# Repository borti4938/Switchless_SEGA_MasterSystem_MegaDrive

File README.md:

### Switchless Mods for SEGA MasterSystem and MegaDrive
---

This is a collection of earlier projects. These projects are not under development anymore. Documentation is rather simple and can be found in source code comments in most cases.

Please don't write me for any support. Please reach out to community forums and use the knowledge and experiences there.

Best Regards, Peter

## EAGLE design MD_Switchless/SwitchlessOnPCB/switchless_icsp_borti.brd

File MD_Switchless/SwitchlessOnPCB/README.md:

This small subprject is not initialted be myself. All thanks to this go to user _ArcadeTV_ and user _wshadow_; both members of the [Circuit-Board.de](https://circuit-board.de/forum/) community.
So what is this?

Histroy
---

Once I started designing my own switchless mod for the Sega Mega Drive, ArcadeTV drew a printed circuit board.
Although I was not ready with the implementation, ArcadeTV [published the PCB on circuit-board](https://circuit-board.de/forum/index.php/Thread/14691-Mega-Drive-Mod-Platinen-RGB-Bypass-Switchless-Mod-Mega-Amp/).  
This board is available in this repository.

Time was running and I lost the focus to this PCB.
Instead I made design decisions which made PCB pinout incompatible to my code.
Reasons were being pin compatible to [Sebs popular code](https://knzl.at/saturnmod/), which is used for Multi-BIOS extension on the MegaCD as well as the [build-in-game project](https://github.com/borti4938/MD-Build-In-Game).
The code went into a final state as it is presented in the top-folder here in the repository.
Another long time period passed by.

CiBo user wshadow [picked up both](https://circuit-board.de/forum/index.php/Thread/14691-Mega-Drive-Mod-Platinen-RGB-Bypass-Switchless-Mod-Mega-Amp/?postID=736815#post736815) - the PCB and code - and made both compatible again.
He worked hard, learned assembler, and finally made it.
I reviewed the changes and now publish code and PCB.

Notes
---

I don't own a Mega Drive!
So please be patient if there are any misstakes in the text comming from my misunderstanding.

### PCB

PCB is made with EAGLE and has two layers.
I tested to upload the PCB on OSHPark and it works.
Of course, you can also use any other PCB manufacturer you want.

### Parts for PCB and Installation

- 1x RND 1500805Y1041
- 1x BAT 54A SMD
- 1x PIC 16F630-I/SL
- 2x SMD-0805 1,0K
- 1x RND 0805 1 20K
- 2x SMD-0805 220
- 1x RG-LED or RGB-LED with 3mm or 5mm head  
  For installation, Code supports both common anode and common cathod LEDs

### Code

The code is made for the PIC16F630.
There is an ICSP header on the PCB.

### Additional notes

Additional notes can be found in the top comment section of the *.asm file.

### Feedback

Feedback is very welcome!

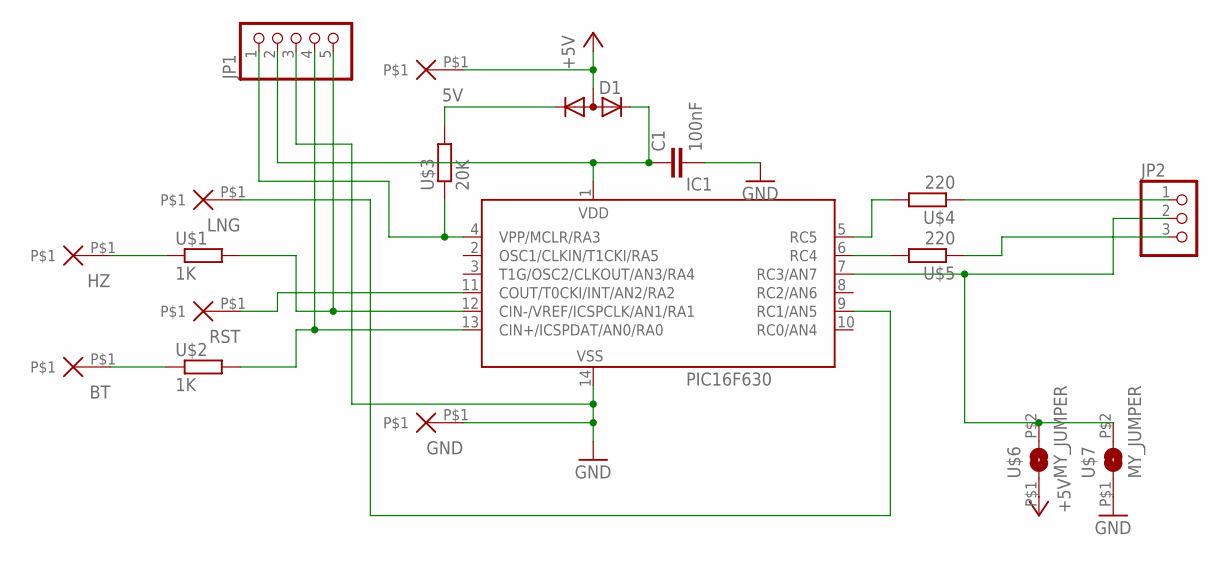
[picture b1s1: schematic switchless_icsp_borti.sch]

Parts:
5V: PAD; PADS
BT: PAD; PADS
C1: 100nF; Z0805
D1: DIODE_CA-AC__; SOT23C
GND: PAD; PADS
HZ: PAD; PADS
IC1: PIC16F630
JP1: PINHD-1X5; 1X05
JP2: PINHD-1X3; 1X03
LNG: PAD; PADS
RST: PAD; PADS
U$1, U$2: 1K; Z0805
U$3: 20K; Z0805
U$4, U$5: 220; Z0805
U$6, U$7: MY_JUMPER; MYJUMP

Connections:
+5V: 5V.P$1, D1.3 (A), U$6.P$1 (1)
GND: C1.2, GND.P$1, IC1.14 (VSS), JP1.3, U$7.P$1 (1)
unnamed: IC1.5 (RC5), U$4.2
unnamed: IC1.6 (RC4), U$5.2
unnamed: JP2.1, U$4.1
unnamed: JP2.3, U$5.1
unnamed: IC1.9 (RC1/AN5), LNG.P$1
unnamed: IC1.11 (COUT/T0CKI/INT/AN2/RA2), RST.P$1
unnamed: IC1.12 (CIN-/VREF/ICSPCLK/AN1/RA1), JP1.5, U$1.2
unnamed: IC1.13 (CIN+/ICSPDAT/AN0/RA0), JP1.4, U$2.2
unnamed: IC1.4 (VPP/MCLR/RA3), JP1.1, U$3.1
unnamed: HZ.P$1, U$1.1
unnamed: BT.P$1, U$2.1
unnamed: C1.1, D1.2 (K2), IC1.1 (VDD), JP1.2
unnamed: D1.1 (K1), U$3.2
unnamed: IC1.7 (RC3/AN7), JP2.2, U$6.P$2 (2), U$7.P$2 (2)

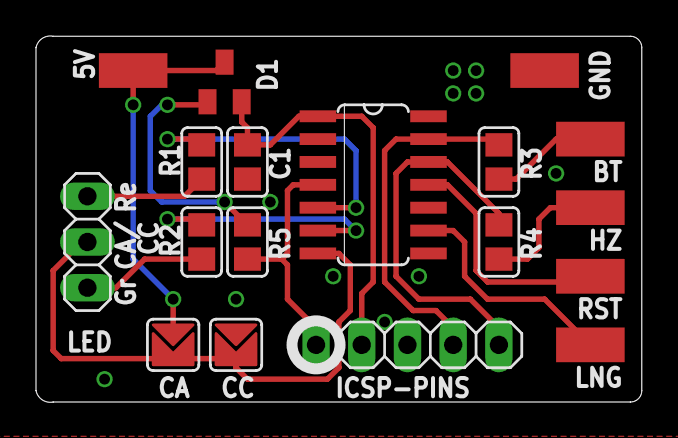
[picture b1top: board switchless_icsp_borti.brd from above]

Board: 2 copper layers, 33.7 x 20.3 mm, 18 parts (0 on the bottom side), 16 nets.

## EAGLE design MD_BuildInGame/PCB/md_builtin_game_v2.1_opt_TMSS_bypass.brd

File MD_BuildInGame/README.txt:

Build-In Game Project for Sega Genesis / Mega Drive  
===================================================  
  
Main idea by ArcadeTV  
Development by srdwa, ArcadeTV and borti4938  
  
See logs and discussions here: http://circuit-board.de/forum/index.php/Thread/17706-Idee-Mega-Drive-mit-eingebautem-Spiel/  
  
===================================================  

This work here is still WIP!!! It has been never tested so far!!!  

===================================================  

Main idea:  
- start a game from internal rom if no device is present at the extension port or no cartridge is present  
- use indentification signals from cart slot and extension slot for detection  
- internal rom can be separated in one, two or four banks (selected by two pins)  
- bank switch is accessed by a 2bit counter  
- TMSS disable mod as described here: http://assemblergames.com/l/threads/md-genny-auto-switching-tmss-bypass-mod.19781/ can be enabled optionally  
  
===================================================  
  
ToDo:  
- test 2bit counter addition for switchless code (code by borti4938)  
- write installation tips  
  
===================================================  
  
Pinout of the PLD (G16V8) as used on the PCB:  
  
/* *************** INPUT PINS ******************** */  
PIN  1 = DISKn;     /* /DISK (ExpPort B2)                       */  
PIN  2 = ROM_Mode2; /* high/open = 1 game     , low = 2 games   */  
PIN  3 = ROM_Mode4; /* high/open = 1/2 game(s), low = 4 games   */  
                    /* low = 4 games (beats ROM_Mode2)          */  
PIN  4 = CARTn;     /* /CART (from ASIC cart slot B32,          */  
                    /*        cutted from ASIC)                 */  
PIN  5 = ASIC_OEn;  /* /OE (from ASIC; cutted from cart slot    */  
                    /*                 B17 if TMSS Mod is used) */  
PIN  6 = CEn;       /* /CE (cart slot B16)                      */  
PIN  7 = A23;       /* A23 (cart slot B11)                      */  
PIN  8 = AMSB0;     /* A19 (cart slot  B7)                      */  
PIN  9 = AMSB1;     /* A20 (cart slot  B8)                      */  
                    /* (addressbus counts from A1)              */  
  
/* *************** I/O PINS ******************** */  
PIN 19 = BIG_Sel0;   /* bank switch LSB                         */  
PIN 18 = BIG_Sel1;   /* bank switch MSB                         */  
PIN 17 = ASIC_CARTn; /* /CART (from ASIC; cutted from cart      */  
                     /*                   slot B32)             */  
PIN 16 = ROM_OEn;    /* /OE internal EEPROM (29F1610 Pin 14)    */  
PIN 15 = ROM_CEn;    /* /CE internal EEPROM (29F1610 Pin 12)    */  
PIN 14 = CART_OEn;   /* /OE cartridge (cart slot B17)           */  
PIN 13 = ROM_AMSB0;  /* A18 internal EEPROM (29F1610 Pin  2)    */  
PIN 12 = ROM_AMSB1;  /* A19 internal EEPROM (29F1610 Pin 43)    */  
PIN 11 = TMSS_ENn;   /* high = disabled, low = enabled          */  
                     /* /M3 (cart slot B30) AND TMSS-Mod_en     */

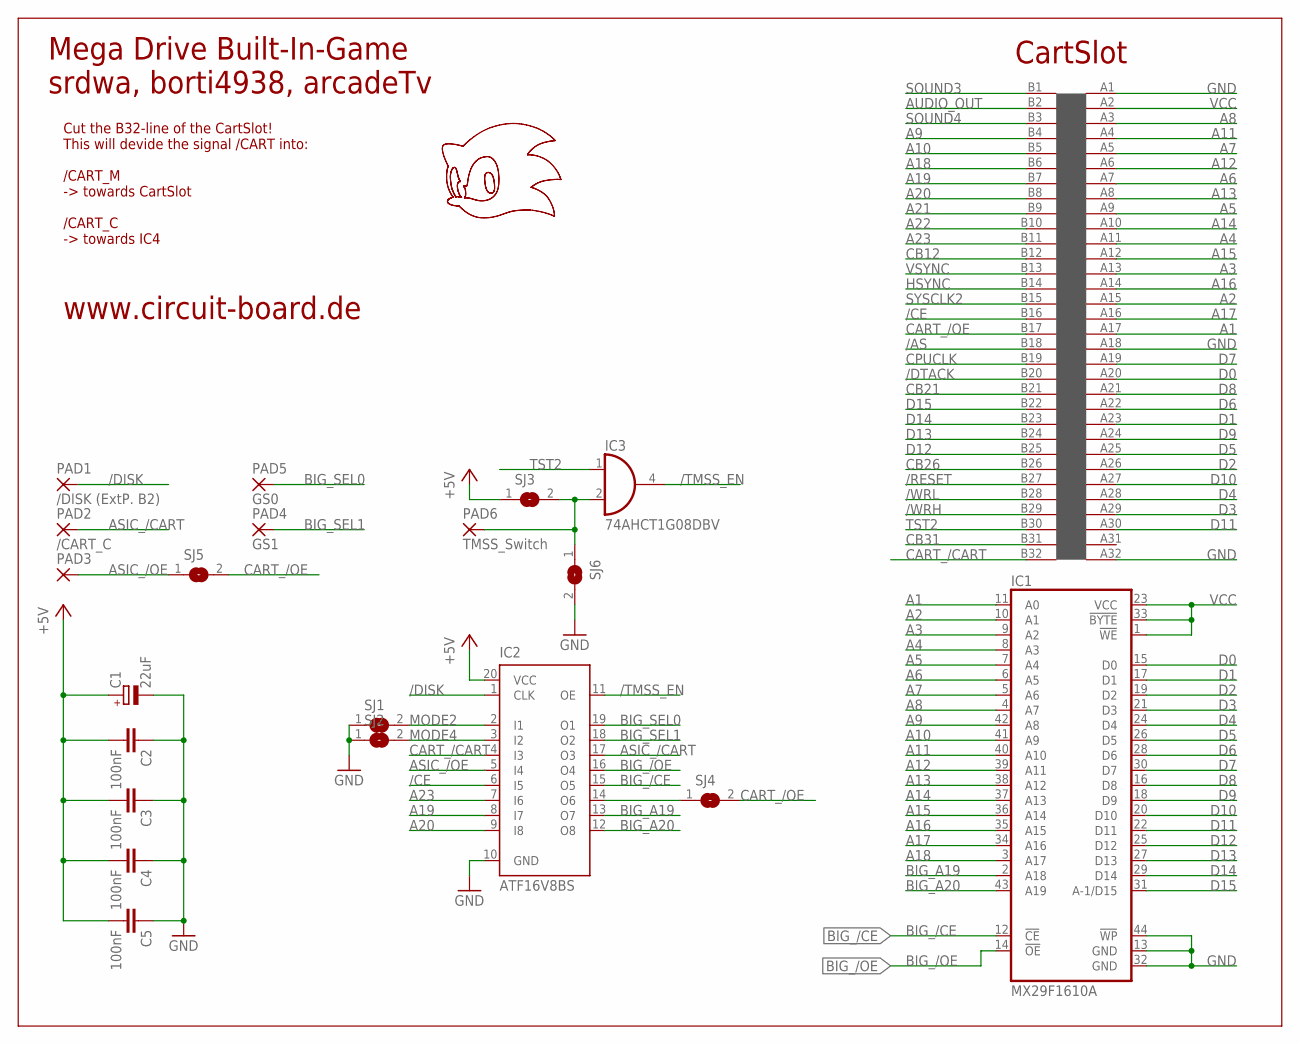
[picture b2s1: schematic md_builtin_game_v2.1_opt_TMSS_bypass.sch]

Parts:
C1: 22uF; SMC_C
C2, C3, C4, C5: 100nF; Z0805
IC1: MX29F1610A; SO44
IC2: ATF16V8BS; SO20L
IC3: 74AHCT1G08DBV; SOT23-5
PAD1: /DISK (ExtP. B2); SMD1,27-2,54
PAD2: /CART_C; SMD1,27-2,54
PAD3: SMD2; SMD1,27-2,54
PAD4: GS1; SMD1,27-2,54
PAD5: GS0; SMD1,27-2,54
PAD6: TMSS_Switch; SMD1,27-2,54
SJ1, SJ2, SJ3, SJ4, SJ5, SJ6: SJ
U$1: LOGO_SONIC_20MM
U$6: MEGADRIVE_EDGE_CONNECTOR

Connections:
/AS: U$6.B18
/CE: IC2.6 (I5), U$6.B16
/DISK: IC2.1 (CLK), PAD1.1
/DTACK: U$6.B20
/RESET: U$6.B27
/TMSS_EN: IC2.11 (OE), IC3.4 (O)
/WRH: U$6.B29
/WRL: U$6.B28
A1: IC1.11 (A0), U$6.A17
A2: IC1.10 (A1), U$6.A15
A3: IC1.9 (A2), U$6.A13
A4: IC1.8 (A3), U$6.A11
A5: IC1.7 (A4), U$6.A9
A6: IC1.6 (A5), U$6.A7
A7: IC1.5 (A6), U$6.A5
A8: IC1.4 (A7), U$6.A3
A9: IC1.42 (A8), U$6.B4
A10: IC1.41 (A9), U$6.B5
A11: IC1.40 (A10), U$6.A4
A12: IC1.39 (A11), U$6.A6
A13: IC1.38 (A12), U$6.A8
A14: IC1.37 (A13), U$6.A10
A15: IC1.36 (A14), U$6.A12
A16: IC1.35 (A15), U$6.A14
A17: IC1.34 (A16), U$6.A16
A18: IC1.3 (A17), U$6.B6
A19: IC2.8 (I7), U$6.B7
A20: IC2.9 (I8), U$6.B8
A21: U$6.B9
A22: U$6.B10
A23: IC2.7 (I6), U$6.B11
ASIC_/CART: IC2.17 (O3), PAD2.1
ASIC_/OE: IC2.5 (I4), PAD3.1, SJ5.1
AUDIO_OUT: U$6.B2
BIG_/CE: IC1.12 (!CE), IC2.15 (O5)
BIG_/OE: IC1.14 (!OE), IC2.16 (O4)
BIG_A19: IC1.2 (A18), IC2.13 (O7)
BIG_A20: IC1.43 (A19), IC2.12 (O8)
BIG_SEL0: IC2.19 (O1), PAD5.1
BIG_SEL1: IC2.18 (O2), PAD4.1
CART_/CART: IC2.4 (I3), U$6.B32
CART_/OE: SJ4.2, SJ5.2, U$6.B17
CB12: U$6.B12
CB21: U$6.B21
CB26: U$6.B26
CB31: U$6.B31
CPUCLK: U$6.B19
D0: IC1.15 (D0), U$6.A20
D1: IC1.17 (D1), U$6.A23
D2: IC1.19 (D2), U$6.A26
D3: IC1.21 (D3), U$6.A29
D4: IC1.24 (D4), U$6.A28
D5: IC1.26 (D5), U$6.A25
D6: IC1.28 (D6), U$6.A22
D7: IC1.30 (D7), U$6.A19
D8: IC1.16 (D8), U$6.A21
D9: IC1.18 (D9), U$6.A24
D10: IC1.20 (D10), U$6.A27
D11: IC1.22 (D11), U$6.A30
D12: IC1.25 (D12), U$6.B25
D13: IC1.27 (D13), U$6.B24
D14: IC1.29 (D14), U$6.B23
D15: IC1.31 (A-1/D15), U$6.B22
GND: C1.-, C2.1, C3.1, C4.1, C5.1, IC1.13 (GND), IC1.32 (GND), IC1.44 (!WP), IC2.10 (GND), IC3.3 (GND), SJ1.1, SJ2.1, SJ6.2, U$6.A1, U$6.A18, U$6.A32
HSYNC: U$6.B14
MODE2: IC2.2 (I1), SJ1.2
MODE4: IC2.3 (I2), SJ2.2
unnamed: IC2.14 (O6), SJ4.1
unnamed: IC3.2 (I1), PAD6.1, SJ3.2, SJ6.1
SOUND3: U$6.B1
SOUND4: U$6.B3
SYSCLK2: U$6.B15
TST2: IC3.1 (I0), U$6.B30
VCC: C1.+, C2.2, C3.2, C4.2, C5.2, IC1.1 (!WE), IC1.23 (VCC), IC1.33 (!BYTE), IC2.20 (VCC), IC3.5 (VCC), SJ3.1, U$6.A2
VSYNC: U$6.B13

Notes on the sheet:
Cut the B32-line of the CartSlot! This will devide the signal /CART into: /CART_M -> towards CartSlot /CART_C -> towards IC4
Mega Drive Built-In-Game srdwa, borti4938, arcadeTv
CartSlot
www.circuit-board.de

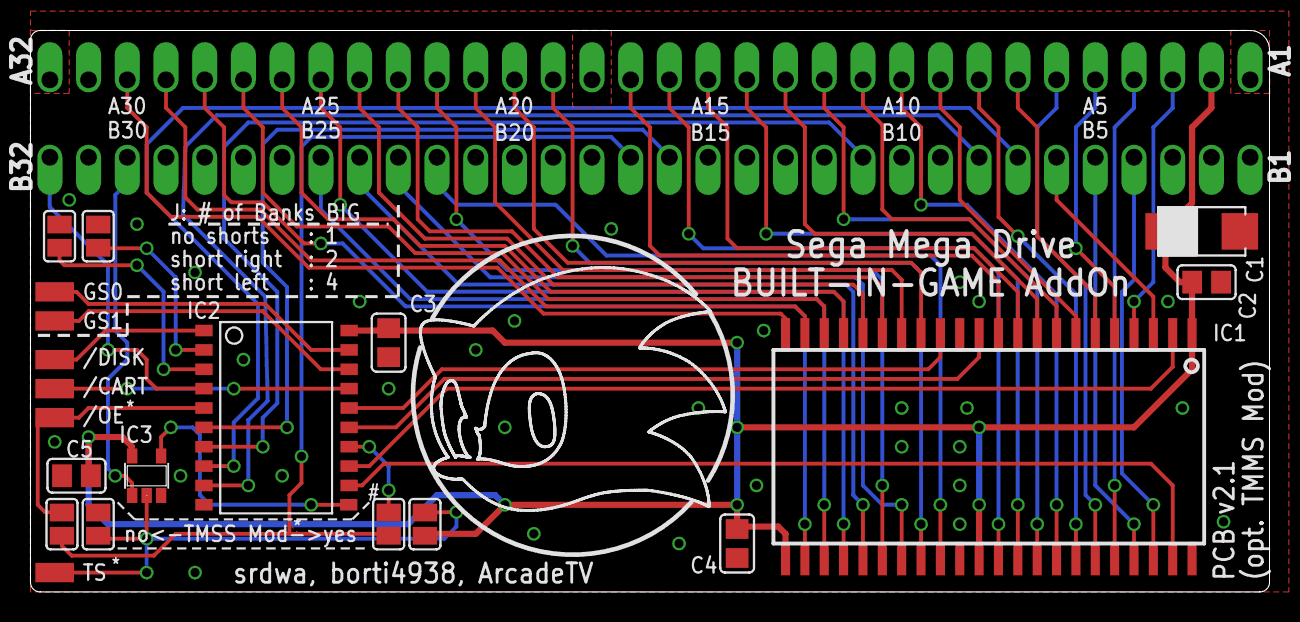
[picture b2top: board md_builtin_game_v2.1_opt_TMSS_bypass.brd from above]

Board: 2 copper layers, 81.3 x 36.8 mm, 22 parts (0 on the bottom side), 57 nets.

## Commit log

2020-05-03 initial commit for archive
